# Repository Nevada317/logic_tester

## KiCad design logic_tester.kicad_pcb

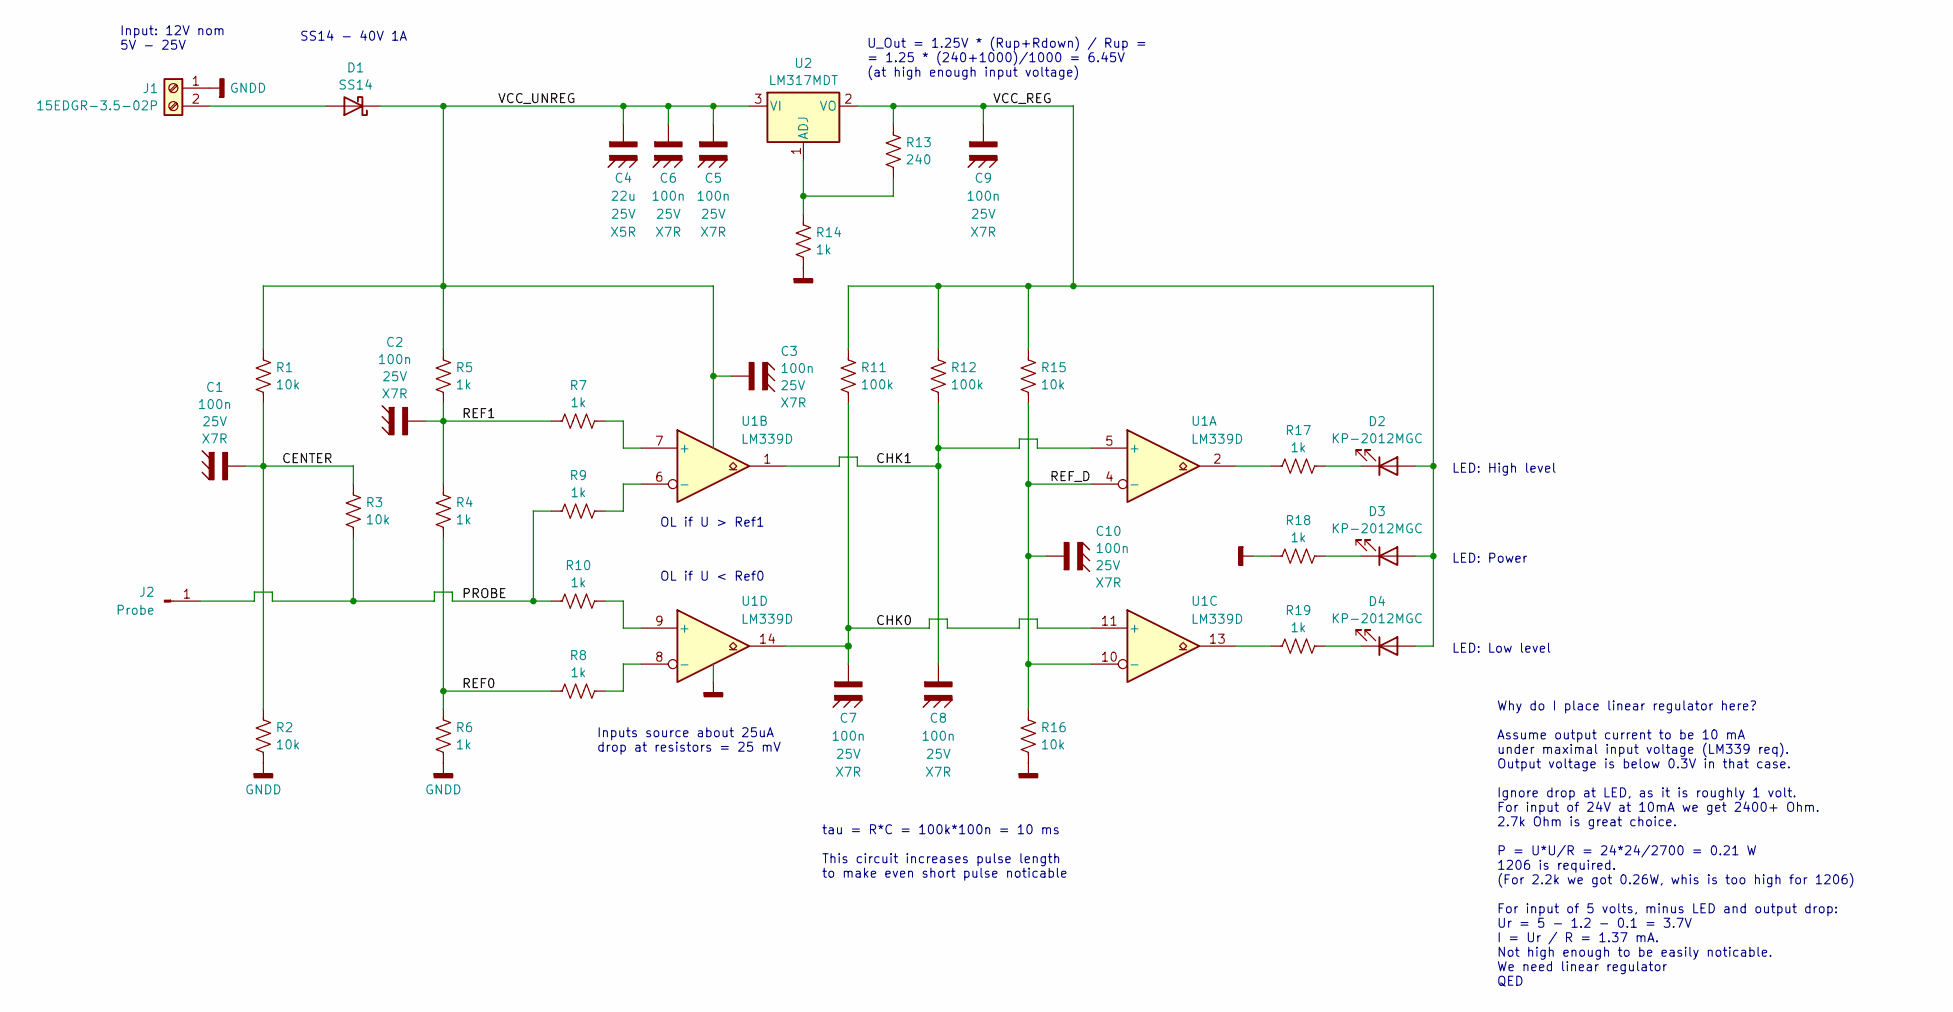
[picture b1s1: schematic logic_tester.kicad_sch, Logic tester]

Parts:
C1, C2, C3, C5, C6, C7, C8, C9, C10: 100n; C_0402; Voltage 25V
C4: 22u; C_1206; Voltage 25V
D1: SS14; DO-214AC_SMA
D2, D3, D4: KP-2012MGC; LED_KP-2012G
J1: 15EDGR-3.5-02P; Terminal_3.5mm_x2
J2: Probe; Pad_Wire
R1, R2, R3, R15, R16: 10k; R_0603
R4, R5, R6, R7, R8, R9, R10, R14, R17, R18, R19: 1k; R_0603
R11, R12: 100k; R_0603
R13: 240; R_0603
U1: LM339D; SOIC-14
U2: LM317MDT; D-PAK

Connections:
/CENTER: C1.1, R1.2, R2.1, R3.1
/CHK0: C7.1, R11.2, U1.11 (+), U1.14
/CHK1: C8.1, R12.2, U1.1, U1.5 (+)
/PROBE: J2.1, R3.2, R9.1, R10.1
/REF0: R4.2, R6.1, R8.1
/REF1: C2.1, R4.1, R5.2, R7.1
/REF_D: C10.1, R15.2, R16.1, U1.4 (-), U1.10 (-)
/VCC_REG: C9.1, D2.2 (A), D3.2 (A), D4.2 (A), R11.1, R12.1, R13.1, R15.1, U2.2 (VO)
GNDD: C1.2 (GNDD), C2.2 (GNDD), C3.2 (GNDD), C4.2 (GNDD), C5.2 (GNDD), C6.2 (GNDD), C7.2 (GNDD), C8.2 (GNDD), C9.2 (GNDD), C10.2 (GNDD), J1.1, R2.2, R6.2, R14.2, R16.2, R18.1, U1.12 (V-)
unnamed: D1.2 (A), J1.2
unnamed: D2.1 (K), R17.2
unnamed: D3.1 (K), R18.2
unnamed: D4.1 (K), R19.2
unnamed: R17.1, U1.2
unnamed: R19.1, U1.13
unnamed: R7.2, U1.7 (+)
unnamed: R9.2, U1.6 (-)
unnamed: R10.2, U1.9 (+)
unnamed: R8.2, U1.8 (-)
unnamed: R13.2, R14.1, U2.1 (ADJ)
V+: C3.1, C4.1, C5.1, C6.1, D1.1 (K), R1.1, R5.1, U1.3 (V+), U2.3 (VI)

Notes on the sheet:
Input: 12V nom 5V - 25V
SS14 - 40V 1A
OL if U > Ref1
LED: Power
Inputs source about 25uA drop at resistors = 25 mV
U_Out = 1.25V * (Rup+Rdown) / Rup = = 1.25 * (240+1000)/1000 = 6.45V (at high enough input voltage)
OL if U < Ref0
Why do I place linear regulator here? Assume output current to be 10 mA under maximal input voltage (LM339 req). Output voltage is below 0.3V in that case. Ignore drop at LED, as it is roughly 1 volt. For input of 24V at 10mA we get 2400+ Ohm. 2.7k Ohm is great choice. P = U*U/R = 24*24/2700 = 0.21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
tau = R*C = 100k*100n = 10 ms This circuit increases pulse length to make even short pulse noticable
LED: High level
LED: Low level

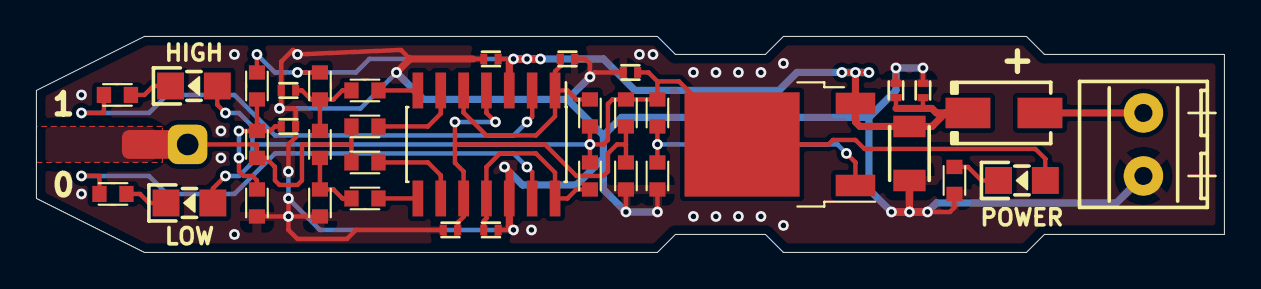
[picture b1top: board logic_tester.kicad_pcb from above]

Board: 2 copper layers, 66.0 x 12.0 mm, 37 parts (0 on the bottom side), 21 nets.

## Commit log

2024-11-22 Empty project
2024-11-22 Schematic idea drafted
2024-11-22 Leds with direct supply - bad idea
2024-11-22 Voltage regulator added
2024-11-22 Capacitors chosen
2024-11-22 Schematics looks OK
2024-11-22 PCB placement started
2024-11-22 Geo reannotate
2024-11-22 Swap comparators for easier routing
2024-11-22 Input circuits layout stub
2024-11-22 Second cascade of comparators placed
2024-11-22 Seems fitted
2024-11-22 Tighter capacitor placement
2024-11-22 Probe pad added
2024-11-22 Signal part routed
2024-11-22 Routing done. PCB shortened
2024-11-22 Size changed: 66x12
2024-11-22 Silk work
2024-11-22 Ground plane + more silk
2024-11-22 Extra mask opening
2024-11-22 Title added to sheets
2024-11-23 QR code added (generated by nayuki.io)
2024-11-23 Gerbers exported
2024-11-23 Schematic exported
2024-11-23 STEP exported
2024-11-23 Images added
